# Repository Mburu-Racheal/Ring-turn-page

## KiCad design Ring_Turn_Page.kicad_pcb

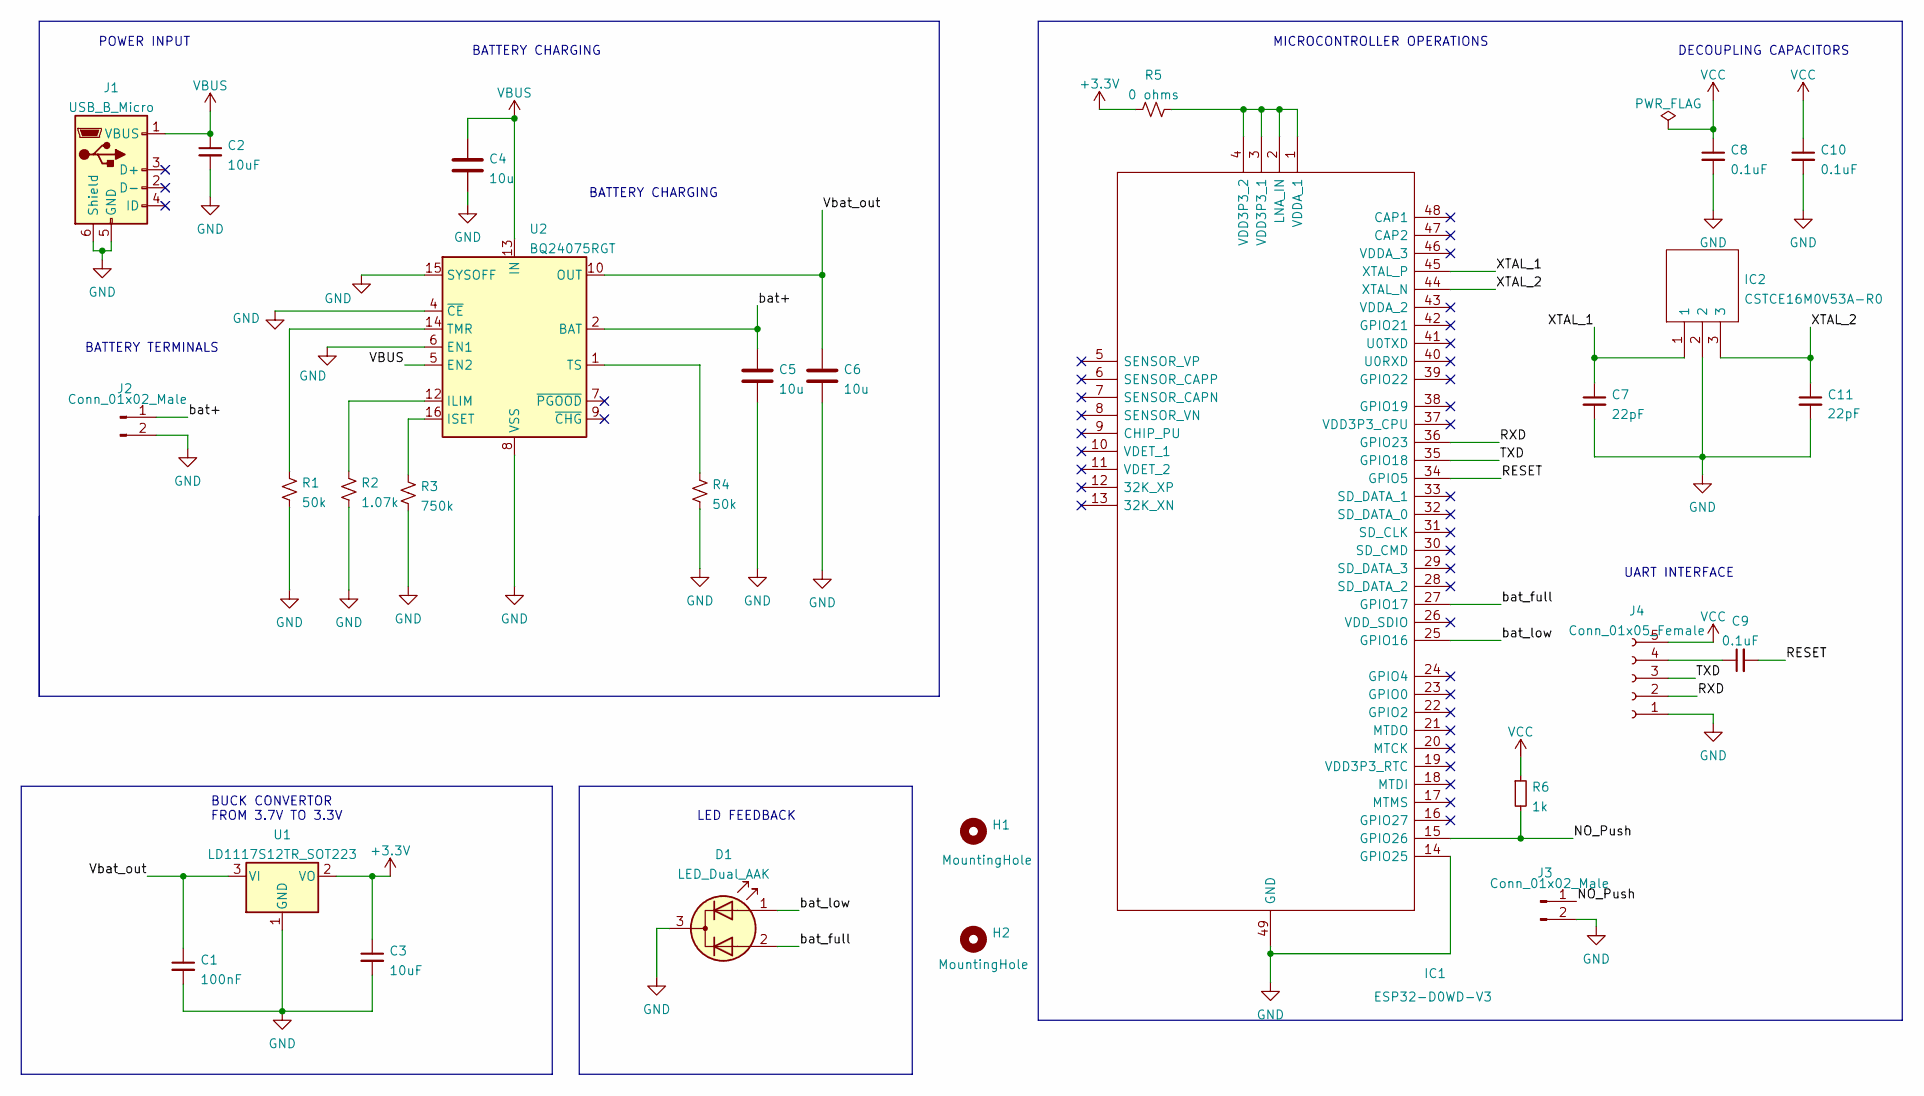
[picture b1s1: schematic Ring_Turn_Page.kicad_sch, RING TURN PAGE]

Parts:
C1: 100nF; C_0603_1608Metric
C2, C3: 10uF; C_0603_1608Metric
C4, C5, C6: 10u; C_0201_0603Metric
C7, C11: 22pF; C_0603_1608Metric
C8, C9, C10: 0.1uF; C_0603_1608Metric
D1: LED_Dual_AAK; LED-L1T2_LUMILEDS
H1, H2: MountingHole; MountingHole_2.1mm
IC1: ESP32-D0WD-V3; QFN35P500X500X90-49N-D; Manufacturer_Part_Number ESP32-D0WD-V3; Mouser Part Number 356-ESP32-D0WD-V3
IC2: CSTCE16M0V53A-R0; CSTCE-V_1; Manufacturer_Part_Number CSTCE16M0V53A-R0; Mouser Part Number 81-CSTCE16M0V53A-R0
J1: USB_B_Micro; USB_Micro-B_Amphenol_10104110_Horizontal
J2: Conn_01x02_Male; SolderJumper-2_P1.3mm_Bridged2Bar_Pad1.0x1.5mm
J3: Conn_01x02_Male; SolderJumper-2_P1.3mm_Bridged_Pad1.0x1.5mm
J4: Conn_01x05_Female; PinHeader_1x05_P2.54mm_Vertical
R1, R4: 50k; R_0603_1608Metric
R2: 1.07k; R_0603_1608Metric
R3: 750k; R_0603_1608Metric
R5: 0 ohms; R_0603_1608Metric
R6: 1k; R_0603_1608Metric
U1: LD1117S12TR_SOT223; SOT-223-3_TabPin2
U2: BQ24075RGT; VQFN-16-1EP_3x3mm_P0.5mm_EP1.6x1.6mm

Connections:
+3V3: C3.1, R5.1, U1.2 (VO)
/NO_Push: IC1.15 (GPIO26), J3.1, R6.2
/RESET: C9.2, IC1.34 (GPIO5)
/RXD: IC1.36 (GPIO23), J4.2
/TXD: IC1.35 (GPIO18), J4.3
/Vbat_out: C1.1, C6.1, U1.3 (VI), U2.10 (OUT), U2.11 (OUT)
/XTAL_1: C7.1, IC1.45 (XTAL_P), IC2.1
/XTAL_2: C11.1, IC1.44 (XTAL_N), IC2.3
/bat+: C5.1, J2.1, U2.2 (BAT), U2.3 (BAT)
/bat_full: D1.2 (A2), IC1.27 (GPIO17)
/bat_low: D1.1 (A1), IC1.25 (GPIO16)
GND: C1.2, C2.2, C3.2, C4.2, C5.2, C6.2, C7.2, C8.2, C10.2, C11.2, D1.3 (K), IC1.14 (GPIO25), IC1.49 (GND), IC2.2, J1.5 (GND), J1.6 (Shield), J2.2, J3.2, J4.1, R1.2, R2.2, R3.2, R4.2, U1.1 (GND), U2.4 (~CE), U2.6 (EN1), U2.8 (VSS), U2.15 (SYSOFF), U2.17 (VSS)
unnamed: C9.1, J4.4
unnamed: IC1.1 (VDDA_1), IC1.2 (LNA_IN), IC1.3 (VDD3P3_1), IC1.4 (VDD3P3_2), R5.2
unnamed: R1.1, U2.14 (TMR)
unnamed: R2.1, U2.12 (ILIM)
unnamed: R3.1, U2.16 (ISET)
unnamed: R4.1, U2.1 (TS)
VBUS: C2.1, C4.1, J1.1 (VBUS), U2.5 (EN2), U2.13 (IN)
VCC: C8.1, C10.1, J4.5, R6.1

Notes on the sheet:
BUCK CONVERTOR FROM 3.7V TO 3.3V
POWER INPUT
BATTERY TERMINALS
DECOUPLING CAPACITORS
BATTERY CHARGING
UART INTERFACE
BATTERY CHARGING
LED FEEDBACK
MICROCONTROLLER OPERATIONS

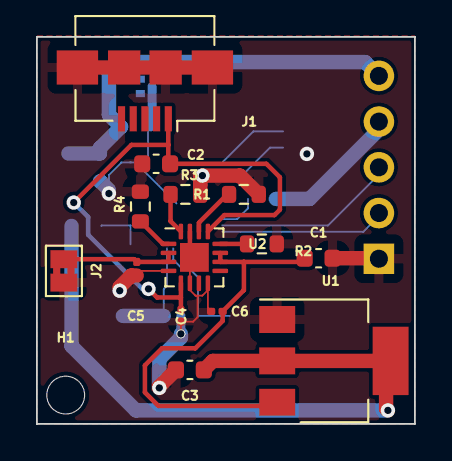
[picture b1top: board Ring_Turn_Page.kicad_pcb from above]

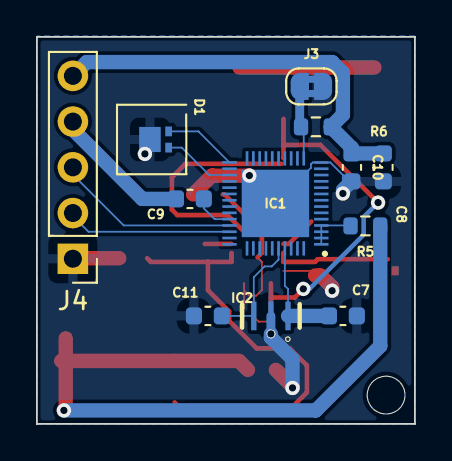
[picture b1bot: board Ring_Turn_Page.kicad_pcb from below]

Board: 2 copper layers, 21.0 x 21.5 mm, 27 parts (12 on the bottom side), 20 nets.
